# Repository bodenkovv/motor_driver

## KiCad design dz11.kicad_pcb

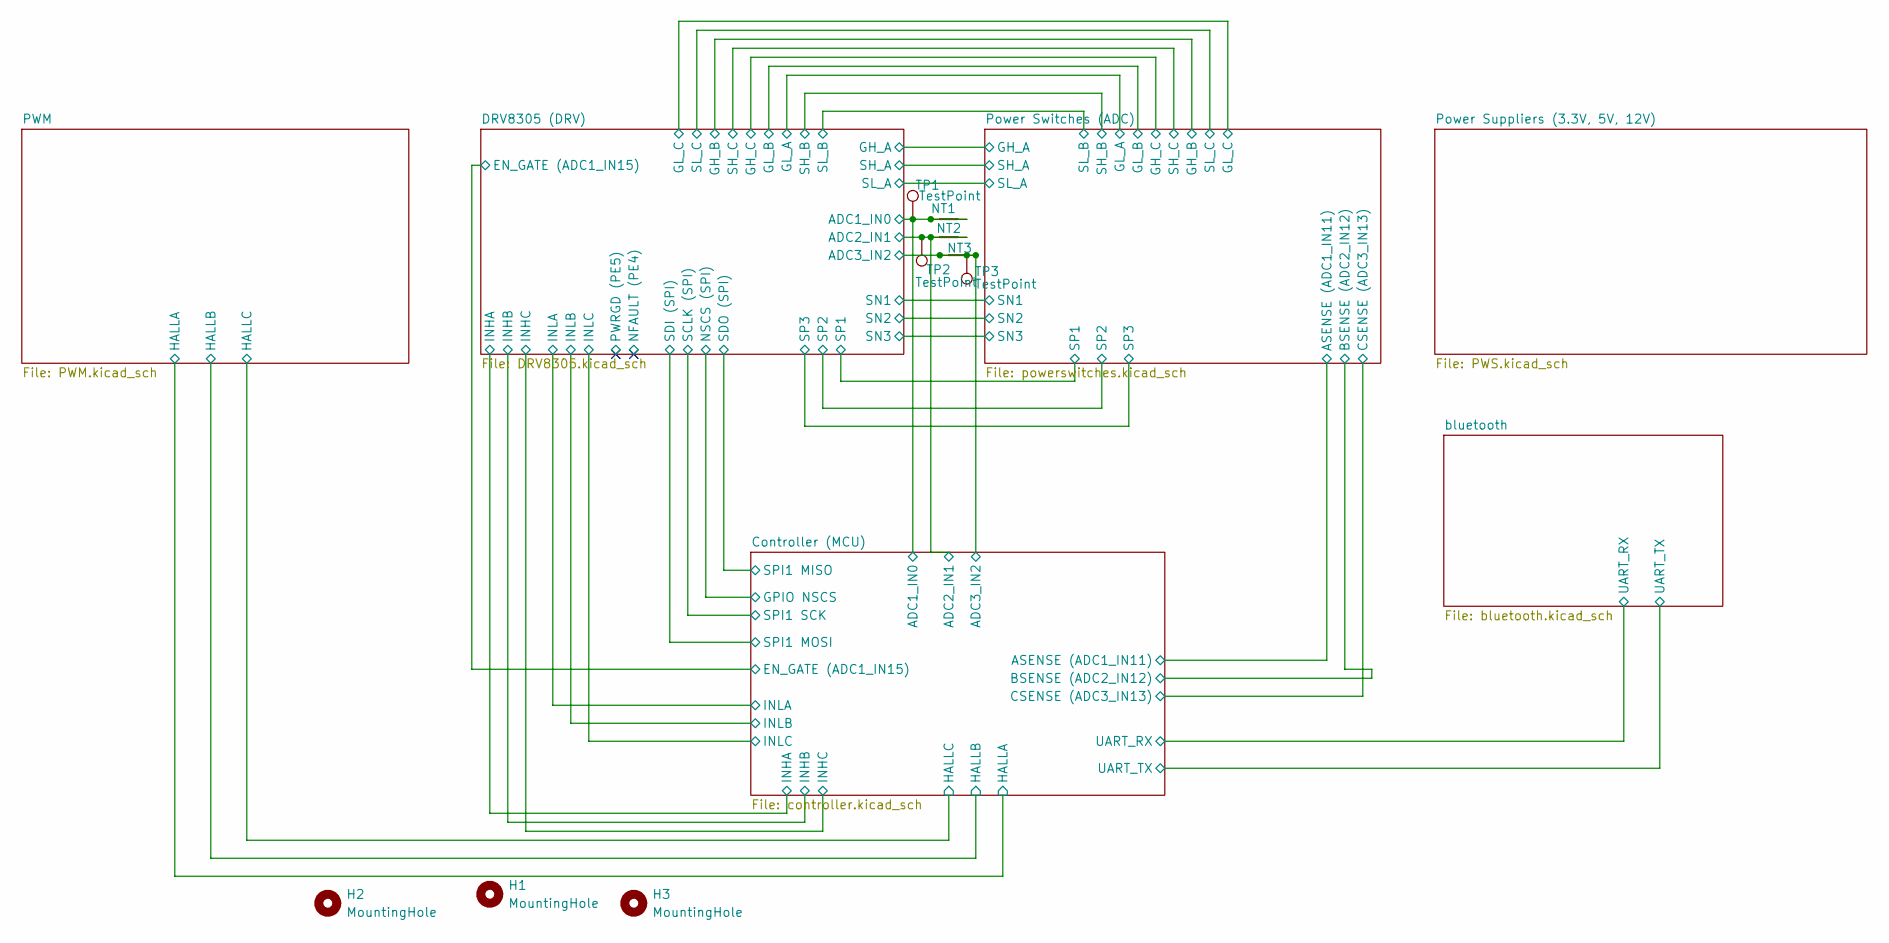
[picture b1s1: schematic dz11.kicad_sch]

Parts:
H1, H2, H3: MountingHole; MountingHole_3.2mm_M3
NT1: NetTie_2; NetTie-2_SMD_Pad0.5mm
NT2: NT2; NetTie-2_SMD_Pad0.5mm
NT3: NT3; NetTie-2_SMD_Pad0.5mm
TP1, TP2, TP3: TestPoint; Pin_D0.7mm_L6.5mm_W1.8mm_FlatFork

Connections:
GND: NT1.1, NT1.2, NT2.1, NT2.2, NT3.1, NT3.2, TP1.1 (1_1), TP2.1 (1_1), TP3.1 (1_1); also elsewhere on the board

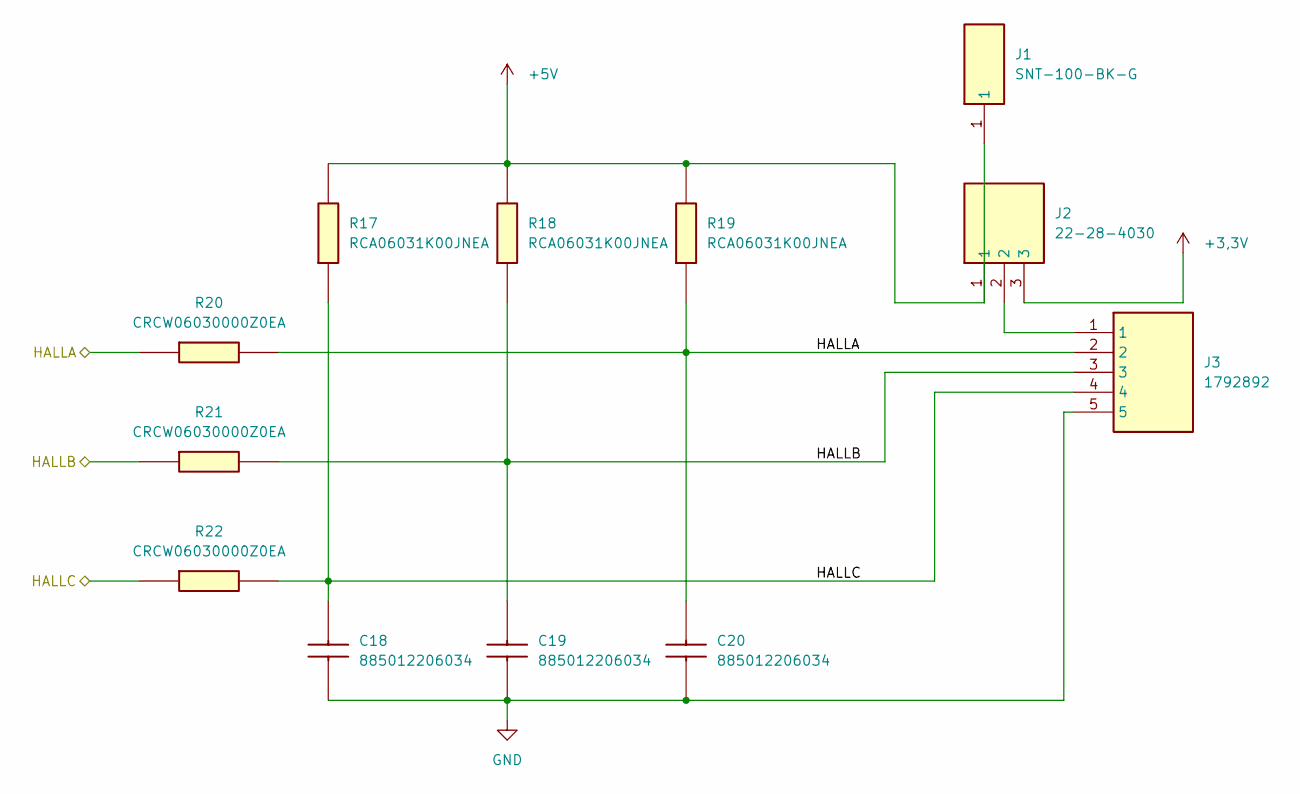
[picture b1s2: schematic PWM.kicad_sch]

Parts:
C18, C19, C20: 885012206034; CAPC1608X80N; Manufacturer_Part_Number 885012206034; Mouser Part Number 710-885012206034
J1: SNT-100-BK-G; HDRV1W100P100X300_1X1_100X100X100P; Manufacturer_Part_Number SNT-100-BK-G; Mouser Part Number 200-SNT100BKG
J2: 22-28-4030; HDRV3W66P0X254_1X3_762X229X838P; Manufacturer_Part_Number 22-28-4030; Mouser Part Number 538-22-28-4030
J3: 1792892; Manufacturer_Part_Number 1792892; Mouser Part Number 651-1792892
R17, R18, R19: RCA06031K00JNEA; RESC1608X50N; Manufacturer_Part_Number RCA06031K00JNEA; Mouser Part Number 71-RCA06031K00JNEA
R20, R21, R22: CRCW06030000Z0EA; RESC1608X50N; Manufacturer_Part_Number CRCW06030000Z0EA; Mouser Part Number 71-CRCW0603-0-E3

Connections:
+3,3V: J2.3; also elsewhere on the board
+5V: J1.1 (1_1), J2.1, R17.2, R18.2, R19.2; also elsewhere on the board
/Controller (MCU)/HALLA: C20.2, J3.2, R19.1, R20.1, R20.2; also elsewhere on the board
/Controller (MCU)/HALLB: C19.2, J3.3, R18.1, R21.1, R21.2; also elsewhere on the board
/Controller (MCU)/HALLC: C18.2, J3.4, R17.1, R22.1, R22.2; also elsewhere on the board
GND: C18.1, C19.1, C20.1, J3.5; also elsewhere on the board
unnamed: J2.2, J3.1

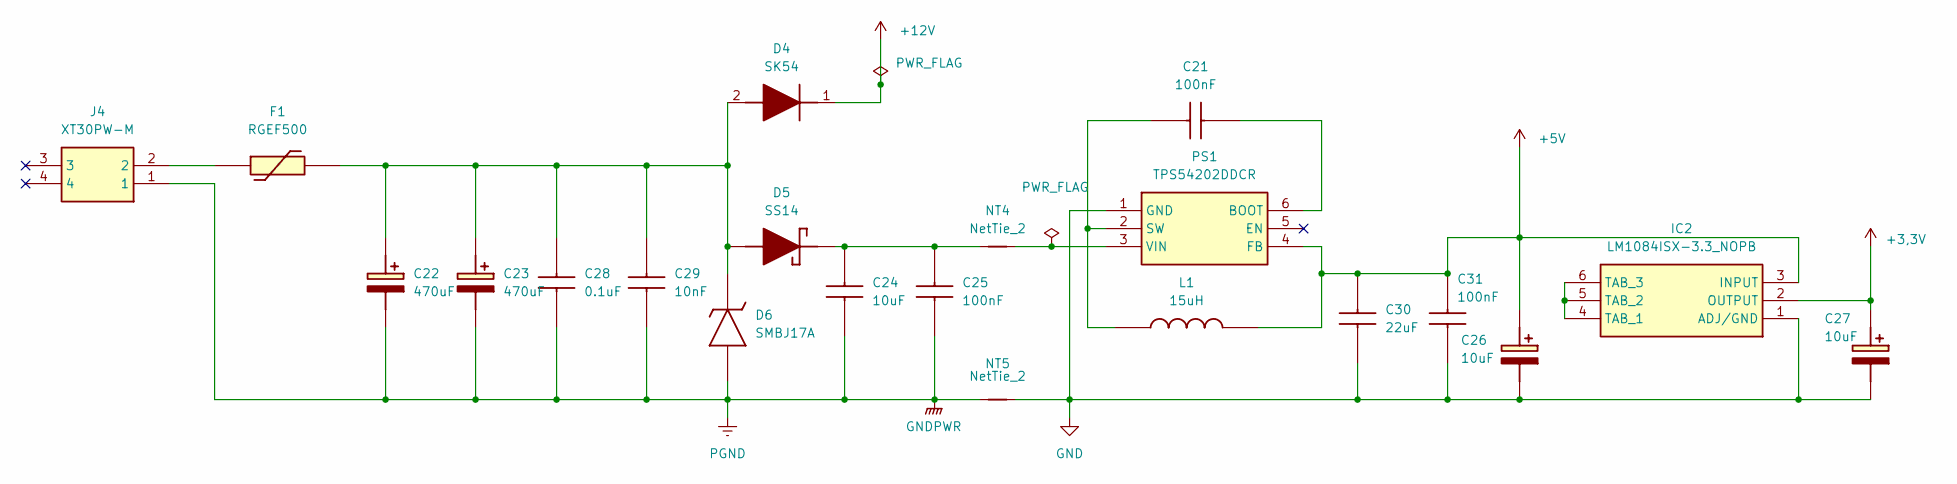
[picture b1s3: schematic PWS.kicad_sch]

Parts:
C21: 100nF; CAPC1608X90N; Manufacturer_Part_Number 06033C104KAT2A; Mouser Part Number 581-06033C104KAT2A
C22, C23: 470uF; CAPPRD500W60D1050H1750; Mouser Part Number 594-MAL219056471E3
C24: 10uF; CAPC1608X90N; Manufacturer_Part_Number CGA3E2X7R1H104K080AA; Mouser Part Number 810-CGA3E2X7R1H104K
C25: 100nF; CAPC3225X230N; Manufacturer_Part_Number C3225X7R1H106M250AC; Mouser Part Number 810-C3225X7R1H106MAC
C26, C27: 10uF; CAPPM3216X180N; Manufacturer_Part_Number 293D106X0010A2TE3; Mouser Part Number 74-293D106X0010A2TE3
C28: 0.1uF; CAPC1608X90N; Manufacturer_Part_Number CGA3E2X7R1H104K080AA; Mouser Part Number 810-CGA3E2X7R1H104K
C29: 10nF; CAPC1005X55N; Manufacturer_Part_Number C1005X8R1E103K050BA
C30: 22uF; CAPC2114X95N; Manufacturer_Part_Number MSASL219LB5226MTNA01
C31: 100nF; CAPC1005X70N; Manufacturer_Part_Number GRM155R71C104KA88D; Mouser Part Number N/A
D4: SK54; DIOM7959X262N; Manufacturer_Part_Number SK54
D5: SS14; DIOM5126X250N; Manufacturer_Part_Number SS14; Mouser Part Number 821-SS14
D6: SMBJ17A; DIOM5436X244N; Mouser Part Number 576-SMBJ17A
F1: RGEF500; Mouser Part Number 650-RGEF500
IC2: LM1084ISX-3.3_NOPB; LM7812SXNOPB; Mouser Part Number 926-LM1084ISX33NOPB
J4: XT30PW-M; XT30PWM; Manufacturer_Part_Number XT30PW-M
L1: 15uH; INDPM120120X1020N; Manufacturer_Part_Number MSS1210-153MEB; Mouser Part Number 994-MSS1210-153MEB
NT4, NT5: NetTie_2; NetTie-2_SMD_Pad0.5mm
PS1: TPS54202DDCR; SOT95P280X110-6N; Manufacturer_Part_Number TPS54202DDCR; Mouser Part Number 595-TPS54202DDCR

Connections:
+3,3V: C27.1 (+), IC2.2 (OUTPUT); also elsewhere on the board
+5V: C22.1 (+), C22.2 (-), C23.1 (+), C23.2 (-), C24.2, C25.2, C26.1 (+), C28.1, C28.2, C29.1, C29.2, C30.2, C31.2, D4.1 (K), D4.2 (A), D5.2 (A), D6.1 (K), D6.2 (A), F1.1, F1.2, IC2.3 (INPUT), J4.1, J4.2, L1.2, NT5.1, PS1.4 (FB); also elsewhere on the board
GND: C26.2 (-), C27.2 (-), C30.1, C31.1, IC2.1 (ADJ/GND), NT5.2, PS1.1 (GND); also elsewhere on the board
unnamed: C24.1, C25.1, D5.1 (K), NT4.1
unnamed: IC2.4 (TAB_1), IC2.5 (TAB_2), IC2.6 (TAB_3)
unnamed: C21.2, PS1.6 (BOOT)
unnamed: C21.1, L1.1, PS1.2 (SW)
unnamed: NT4.2, PS1.3 (VIN)

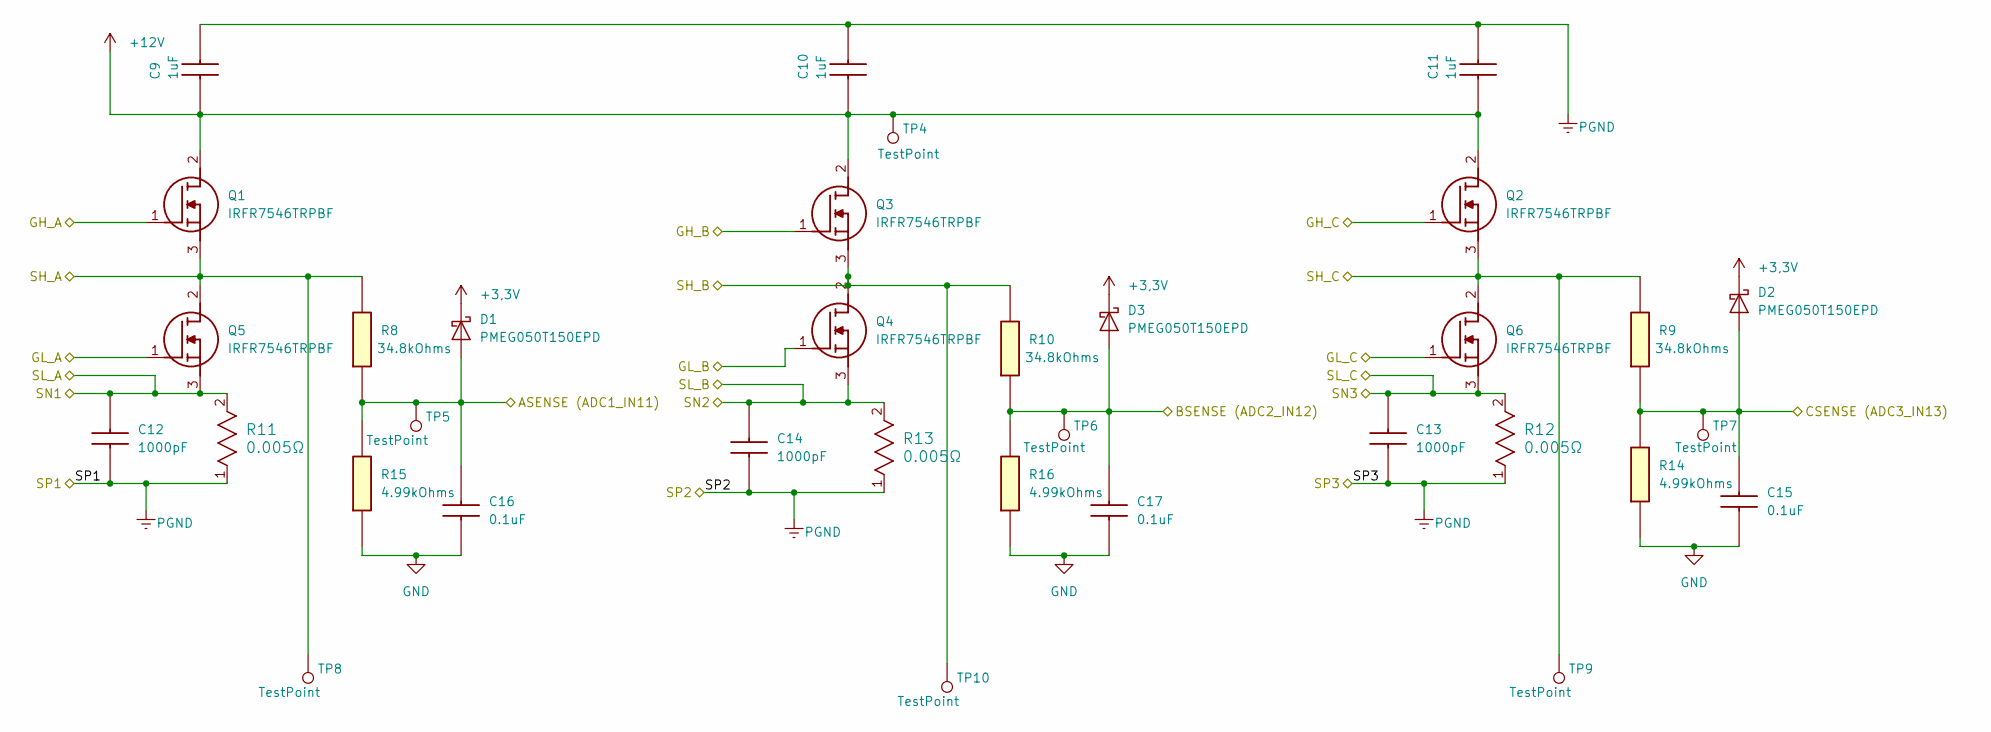
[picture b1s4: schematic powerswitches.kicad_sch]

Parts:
C9, C10, C11: 1uF; CAPC4532X180N; Manufacturer_Part_Number C1812S105K3RACTU
C12, C13, C14: 1000pF; EXFSHR1000PF163V; Manufacturer_Part_Number EXFS/HR 1000PF 1% 63V
C15, C16, C17: 0.1uF; CAPC1608X90N; Manufacturer_Part_Number CGA3E2X7R1H104K080AA; Mouser Part Number 810-CGA3E2X7R1H104K
D1, D2, D3: PMEG050T150EPD; Nexperia_CFP15_SOT-1289
Q1, Q2, Q3, Q4, Q5, Q6: IRFR7546TRPBF; Mouser Part Number 942-IRFR7546TRPBF
R8, R9, R10: 34.8kOhms; RESC2012X60N; Manufacturer_Part_Number RK73H2ATTDD3482D; Mouser Part Number 660-RK73H2ATDD3482D
R11, R12, R13: 0.005Ω; CSS2728
R14, R15, R16: 4.99kOhms; RESC1005X40N; Manufacturer_Part_Number RK73H1ELTP4991F; Mouser Part Number 660-RK73H1ELTP4991F
TP4, TP5, TP6, TP7, TP8, TP9, TP10: TestPoint; Pin_D0.7mm_L6.5mm_W1.8mm_FlatFork

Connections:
+3,3V: D1.3 (K), D2.3 (K), D3.3 (K); also elsewhere on the board
+12V: C9.1, C9.2, C10.1, C10.2, C11.1, C11.2, C12.1, C12.2, C13.1, C13.2, C14.1, C14.2, Q1.2 (D), Q1.3 (S), Q2.2 (D), Q2.3 (S), Q3.2 (D), Q3.3 (S), Q4.2 (D), Q4.3 (S), Q5.2 (D), Q5.3 (S), Q6.2 (D), Q6.3 (S), R8.2, R9.2, R10.2, R11.1, R11.2, R12.1, R12.2, R13.1, R13.2, TP4.1 (1_1), TP8.1 (1_1), TP9.1 (1_1), TP10.1 (1_1); also elsewhere on the board
/DRV8305 (DRV)/GH_A: Q1.1 (G); also elsewhere on the board
/DRV8305 (DRV)/GH_B: Q3.1 (G); also elsewhere on the board
/DRV8305 (DRV)/GH_C: Q2.1 (G); also elsewhere on the board
/DRV8305 (DRV)/GL_A: Q5.1 (G); also elsewhere on the board
/DRV8305 (DRV)/GL_B: Q4.1 (G); also elsewhere on the board
/DRV8305 (DRV)/GL_C: Q6.1 (G); also elsewhere on the board
GND: C15.1, C15.2, C16.1, C16.2, C17.1, C17.2, D1.1 (A), D1.2 (A), D2.1 (A), D2.2 (A), D3.1 (A), D3.2 (A), R8.1, R9.1, R10.1, R14.1, R14.2, R15.1, R15.2, R16.1, R16.2, TP5.1 (1_1), TP6.1 (1_1), TP7.1 (1_1); also elsewhere on the board

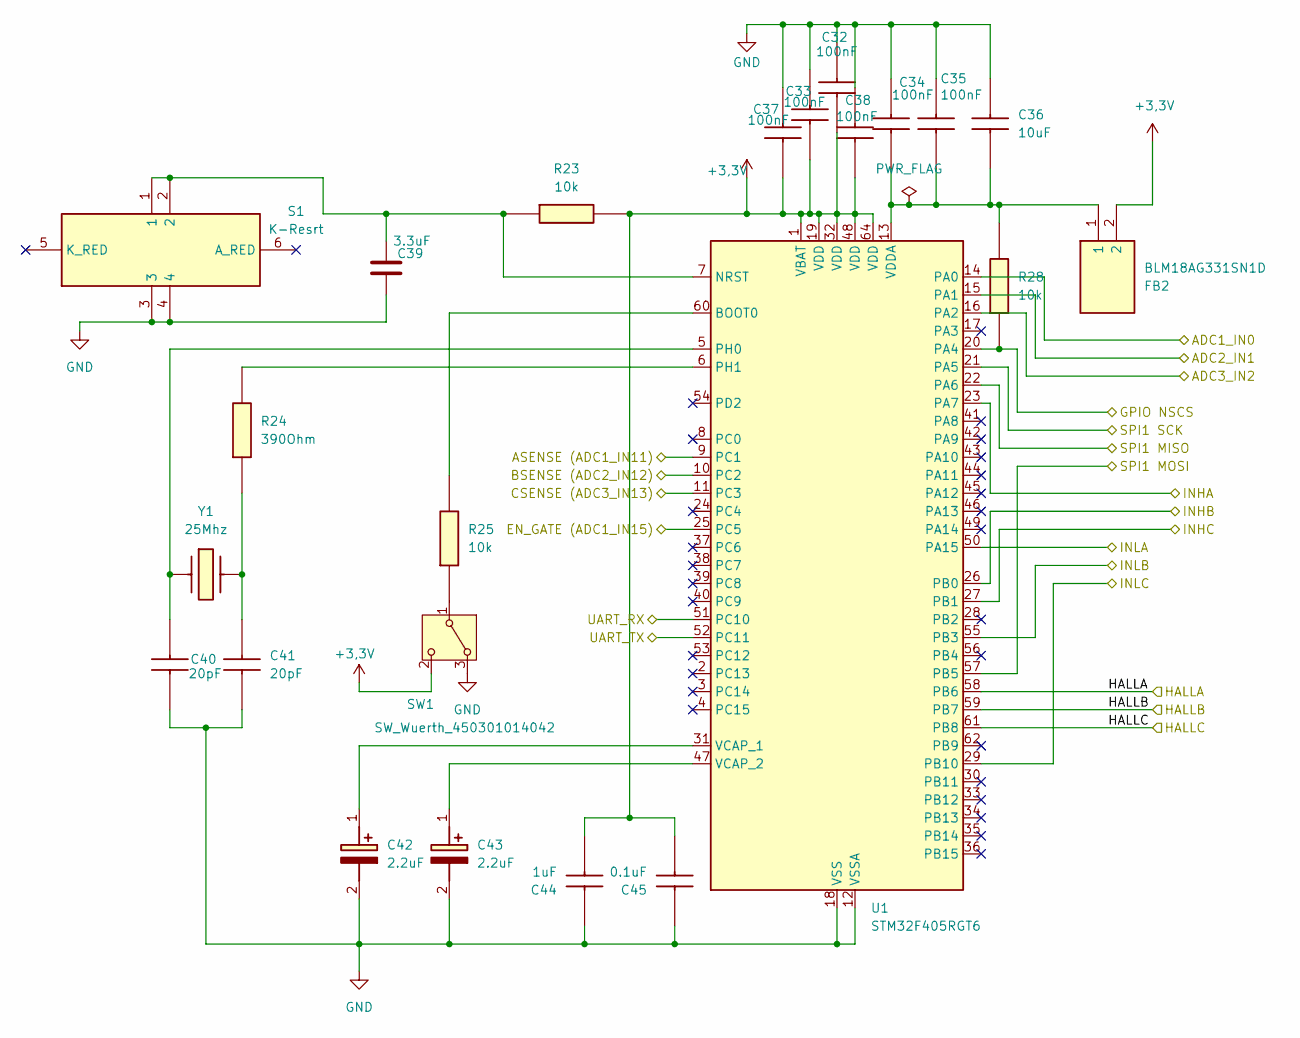
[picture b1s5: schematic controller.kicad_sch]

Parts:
C32, C33, C34, C35, C37, C38: 100nF; CAPC1608X90N; Manufacturer_Part_Number 06033C104KAT2A; Mouser Part Number 581-06033C104KAT2A
C36: 10uF; CAPC3225X230N; Manufacturer_Part_Number C3225X7R1H106M250AC; Mouser Part Number 810-C3225X7R1H106MAC
C39: 3.3uF; C_01005_0402Metric
C40, C41: 20pF; CAPC1005X55N; Manufacturer_Part_Number CC0402GRNPO9BN200; Mouser Part Number 603-CC402GRNPO9BN200
C42, C43: 2.2uF; CAPPM7344X310N; Manufacturer_Part_Number TAJD225M050RNJ
C44: 1uF; CAPC4532X180N; Manufacturer_Part_Number C1812S105K3RACTU
C45: 0.1uF; CAPC1608X90N; Manufacturer_Part_Number CGA3E2X7R1H104K080AA; Mouser Part Number 810-CGA3E2X7R1H104K
FB2: BLM18AG331SN1D; BLM18SP221SN1B; Manufacturer_Part_Number BLM18AG331SN1D; Mouser Part Number 81-BLM18AG331SN1D
R23, R25, R28: 10k; MCS04020C1003FE000; Mouser Part Number 594-MCS04020F1002BE1
R24: 390Ohm; ERJS08_U08__1206_; Mouser Part Number RSN1/4W390OHMJT/B
S1: K-Resrt; TL1220R2BBBRRESET; Manufacturer_Part_Number TL1220R2BBBRRESET; Mouser Part Number 612-1220R2BBBRRESET
SW1: SW_Wuerth_450301014042; SW_Slide-03_Wuerth-WS-SLTV_10x2.5x6.4_P2.54mm
U1: STM32F405RGT6; LQFP-64_10x10mm_P0.5mm
Y1: 25Mhz; LFXTAL072100REEL; Manufacturer_Part_Number LFXTAL072100REEL; Mouser Part Number 449-LFXTAL072100REEL

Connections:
+12V: R28.1, U1.20 (PA4); also elsewhere on the board
/Controller (MCU)/HALLA: U1.58 (PB6); also elsewhere on the board
/Controller (MCU)/HALLB: U1.59 (PB7); also elsewhere on the board
/Controller (MCU)/HALLC: U1.61 (PB8); also elsewhere on the board
GND: C32.1, C32.2, C33.1, C33.2, C34.1, C35.1, C36.1, C37.1, C37.2, C38.1, C38.2, C39.1, C39.2, C40.1, C40.2, C41.1, C41.2, C42.1 (+), C42.2 (-), C43.1 (+), C43.2 (-), C44.1, C44.2, C45.1, C45.2, FB2.2, R23.1, R23.2, R24.1, R24.2, R25.2, S1.1, S1.2, S1.3, S1.4, SW1.2 (C), SW1.3 (A), U1.1 (VBAT), U1.5 (PH0), U1.6 (PH1), U1.7 (NRST), U1.9 (PC1), U1.10 (PC2), U1.11 (PC3), U1.12 (VSSA), U1.14 (PA0), U1.15 (PA1), U1.16 (PA2), U1.18 (VSS), U1.19 (VDD), U1.21 (PA5), U1.22 (PA6), U1.23 (PA7), U1.25 (PC5), U1.26 (PB0), U1.27 (PB1), U1.29 (PB10), U1.31 (VCAP_1), U1.32 (VDD), U1.47 (VCAP_2), U1.48 (VDD), U1.50 (PA15), U1.51 (PC10), U1.52 (PC11), U1.55 (PB3), U1.57 (PB5), U1.60 (BOOT0), U1.63 (VSS), U1.64 (VDD), Y1.1 (CRYSTAL_1), Y1.2 (CRYSTAL_2); also elsewhere on the board
unnamed: R25.1, SW1.1 (B)
unnamed: C34.2, C35.2, C36.2, FB2.1, R28.2, U1.13 (VDDA)

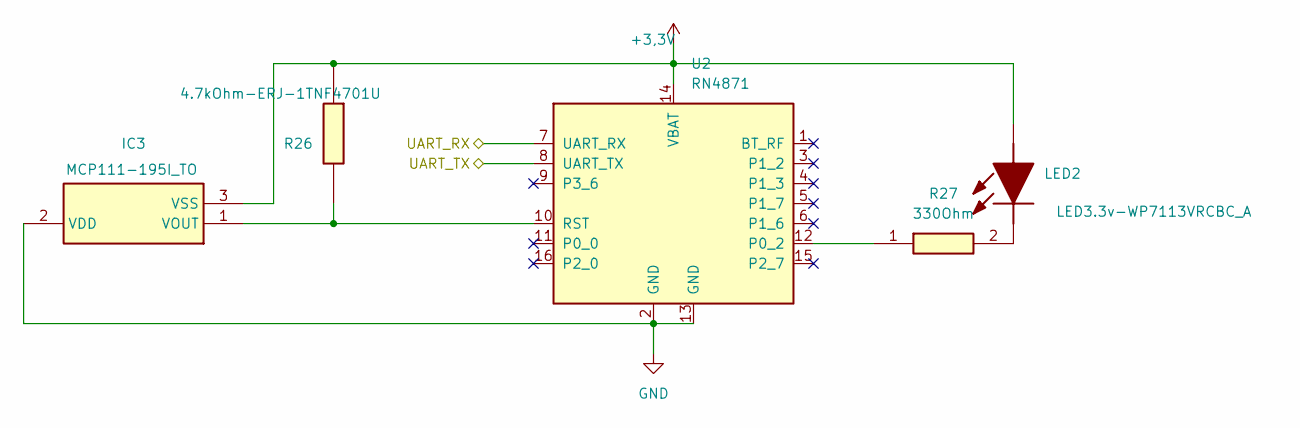
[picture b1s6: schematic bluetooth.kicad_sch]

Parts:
IC3: MCP111-195I_TO; LR645N3GP013; Mouser Part Number 579-MCP111-195I/TO
LED2: LED3.3v-WP7113VRCBC_A; WP7113VRCBCA; Mouser Part Number 604-WP7113VRCBCA
R26: 4.7kOhm-ERJ-1TNF4701U; ERJ1T__2512_; Mouser Part Number 667-ERJ-1TNF4701U
R27: 330Ohm; ERJS08_U08__1206_; Mouser Part Number 667-ERJ-S08J331V
U2: RN4871; Microchip_RN4871

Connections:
+3,3V: IC3.3 (VSS), LED2.2 (A), R26.1, U2.14 (VBAT); also elsewhere on the board
GND: IC3.2 (VDD), U2.2 (GND), U2.7 (UART_RX), U2.8 (UART_TX), U2.13 (GND); also elsewhere on the board
unnamed: IC3.1 (VOUT), R26.2, U2.10 (RST)
unnamed: LED2.1 (K), R27.2
unnamed: R27.1, U2.12 (P0_2)

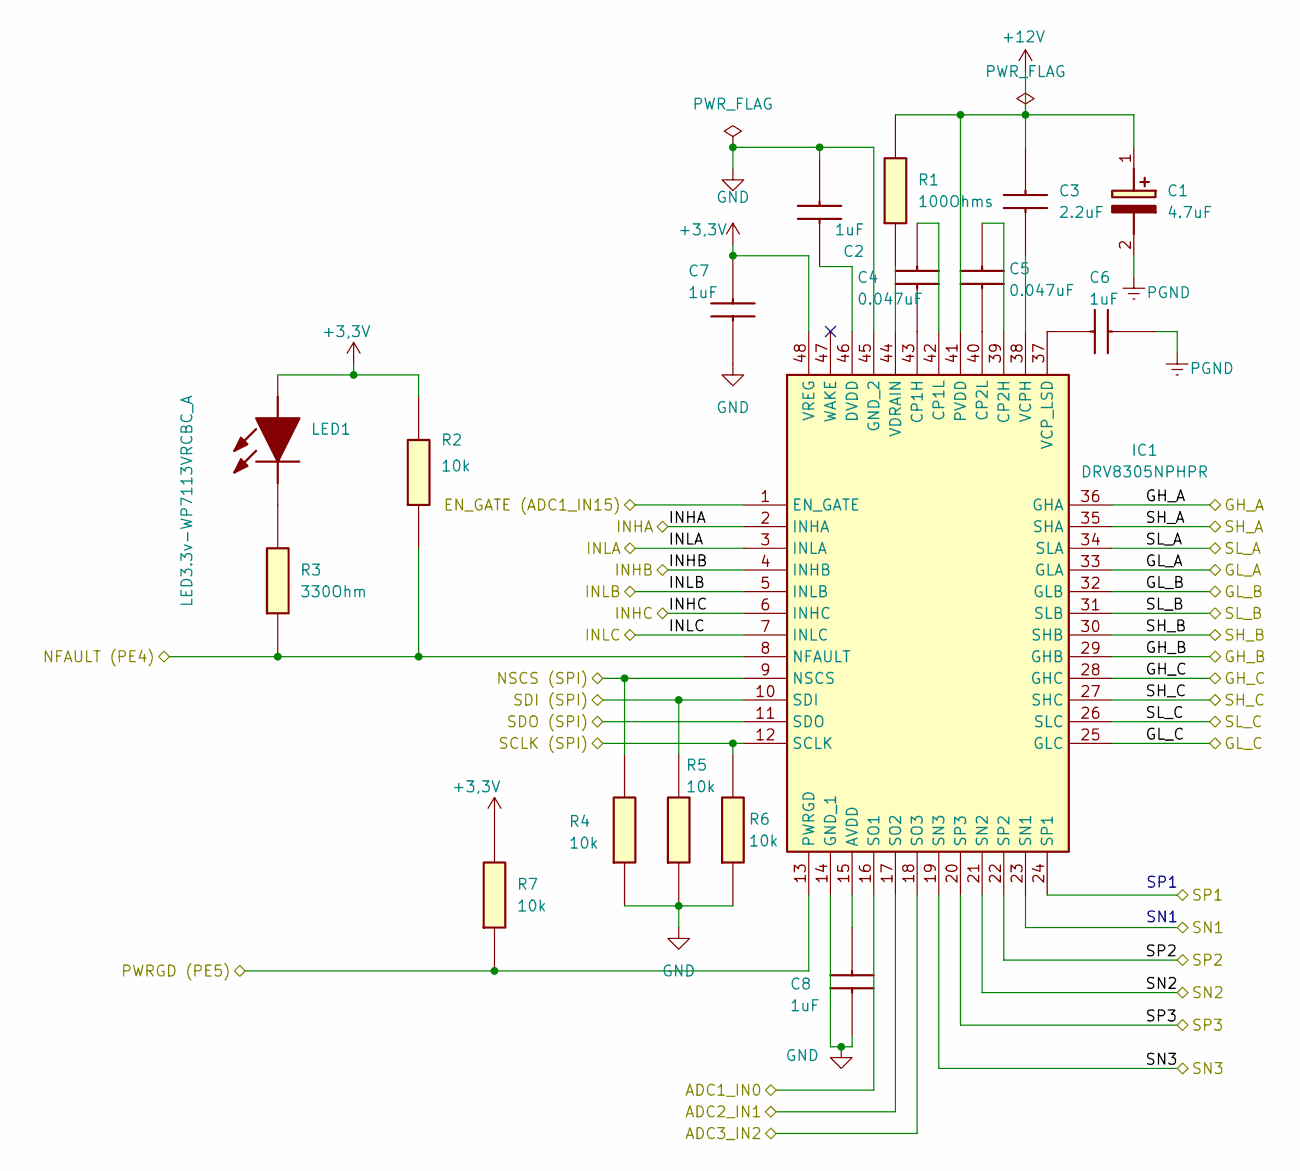
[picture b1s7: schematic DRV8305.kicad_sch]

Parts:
C1: 4.7uF; CAPPM7344X310N; Mouser Part Number 581-TRMD475K050R0200
C2, C6, C7, C8: 1uF; CAPC4532X180N; Manufacturer_Part_Number C1812S105K3RACTU
C3: 2.2uF; GCM21; Manufacturer_Part_Number GCM21BM8EH225KE08L
C4, C5: 0.047uF; GCM31C5C2E183FX03L; Manufacturer_Part_Number GCM31M5C1H473GA16L
IC1: DRV8305NPHPR; QFP50P900X900X120-48N; Manufacturer_Part_Number DRV8305NPHPR; Mouser Part Number 595-DRV8305NPHPR
LED1: LED3.3v-WP7113VRCBC_A; WP7113VRCBCA; Mouser Part Number 604-WP7113VRCBCA
R1: 100Ohms; ERJS14_U14__1210_; Mouser Part Number 667-ERJ-S14J101U
R2, R4, R5, R6, R7: 10k; MCS04020C1003FE000; Mouser Part Number 594-MCS04020F1002BE1
R3: 330Ohm; ERJS08_U08__1206_; Mouser Part Number 667-ERJ-S08J331V

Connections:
+12V: C1.1 (+), C1.2 (-), C2.2, C3.2, C6.2, C7.2, C8.2, IC1.8 (NFAULT), IC1.9 (NSCS), IC1.13 (PWRGD), IC1.15 (AVDD), IC1.19 (SN3), IC1.20 (SP3), IC1.21 (SN2), IC1.22 (SP2), IC1.23 (SN1), IC1.24 (SP1), IC1.26 (SLC), IC1.27 (SHC), IC1.30 (SHB), IC1.31 (SLB), IC1.34 (SLA), IC1.35 (SHA), IC1.41 (PVDD), IC1.46 (DVDD), IC1.48 (VREG), LED1.2 (A), R1.2, R2.1, R2.2, R3.1, R4.2, R7.1, R7.2; also elsewhere on the board
/DRV8305 (DRV)/GH_A: IC1.36 (GHA); also elsewhere on the board
/DRV8305 (DRV)/GH_B: IC1.29 (GHB); also elsewhere on the board
/DRV8305 (DRV)/GH_C: IC1.28 (GHC); also elsewhere on the board
/DRV8305 (DRV)/GL_A: IC1.33 (GLA); also elsewhere on the board
/DRV8305 (DRV)/GL_B: IC1.32 (GLB); also elsewhere on the board
/DRV8305 (DRV)/GL_C: IC1.25 (GLC); also elsewhere on the board
GND: C2.1, C7.1, C8.1, IC1.1 (EN_GATE), IC1.2 (INHA), IC1.3 (INLA), IC1.4 (INHB), IC1.5 (INLB), IC1.6 (INHC), IC1.7 (INLC), IC1.10 (SDI), IC1.11 (SDO), IC1.12 (SCLK), IC1.14 (GND_1), IC1.16 (SO1), IC1.17 (SO2), IC1.18 (SO3), IC1.45 (GND_2), R4.1, R5.1, R5.2, R6.1, R6.2; also elsewhere on the board
unnamed: C4.1, IC1.43 (CP1H)
unnamed: C4.2, IC1.42 (CP1L)
unnamed: C5.2, IC1.39 (CP2H)
unnamed: C5.1, IC1.40 (CP2L)
unnamed: C3.1, IC1.38 (VCPH)
unnamed: C6.1, IC1.37 (VCP_LSD)
unnamed: IC1.44 (VDRAIN), R1.1
unnamed: LED1.1 (K), R3.2

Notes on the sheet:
SP1
SN1

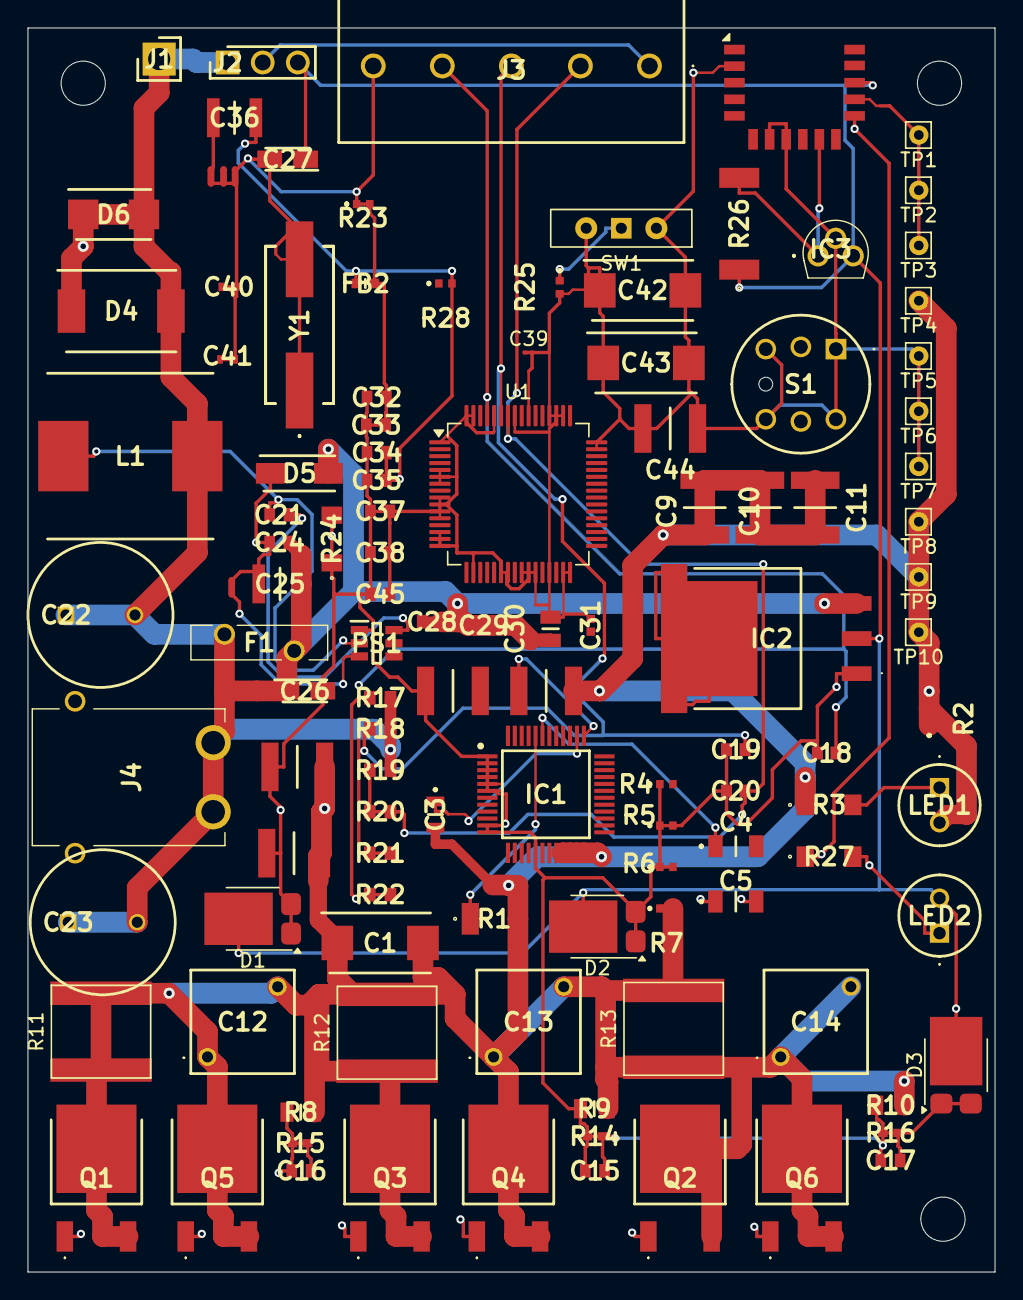
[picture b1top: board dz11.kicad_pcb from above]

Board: 2 copper layers, 70.0 x 90.1 mm, 121 parts (0 on the bottom side), 32 nets.

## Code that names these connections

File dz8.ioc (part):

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Mcu.Name=STM32F405RGTx
Mcu.Package=LQFP64
Mcu.UserName=STM32F405RGTx
PA0-WKUP.Signal=ADCx_IN0
PA1.Signal=ADCx_IN1
PA10.Signal=S_TIM1_CH3
PA13.Mode=JTAG_4_pins
PA13.Signal=SYS_JTMS-SWDIO
PA14.Mode=JTAG_4_pins
PA14.Signal=SYS_JTCK-SWCLK
PA15.Mode=JTAG_4_pins
PA15.Signal=SYS_JTDI
PA2.Signal=ADCx_IN2
PA4.Mode=NSS_Signal_Hard_Output
PA4.Signal=SPI1_NSS
PA5.Mode=Full_Duplex_Master
PA5.Signal=SPI1_SCK
PA6.Mode=Full_Duplex_Master
PA6.Signal=SPI1_MISO
PA7.Mode=PWM Generation1 CH1 CH1N
PA7.Signal=TIM1_CH1N
PA8.Signal=S_TIM1_CH1
PA9.Signal=S_TIM1_CH2
PB0.Mode=PWM Generation2 CH2 CH2N
PB0.Signal=TIM1_CH2N
PB1.Mode=PWM Generation3 CH3 CH3N
PB1.Signal=TIM1_CH3N
PB3.Mode=JTAG_4_pins
PB3.Signal=SYS_JTDO-SWO
PB5.Mode=Full_Duplex_Master
PB5.Signal=SPI1_MOSI
PB6.Signal=S_TIM4_CH1
PB7.Signal=S_TIM4_CH2
PB8.Signal=S_TIM4_CH3
PC1.Signal=ADCx_IN11
PC10.Mode=Asynchronous
PC10.Signal=UART4_TX
PC11.Mode=Asynchronous
PC11.Signal=UART4_RX
PC2.Signal=ADCx_IN12
PC3.Signal=ADCx_IN13
PC5.GPIOParameters=GPIO_Label
PC5.GPIO_Label=EN_GATE
PC5.Signal=ADCx_IN15
RCC.HSE_VALUE=25000000
RCC.SYSCLKFreq_VALUE=16000000
board=custom
